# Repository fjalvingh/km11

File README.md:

# Pdp-11 KM11 Maintenance Module with LCD screen

This is supposed to become a KM11 maintenance module. It is a 2 slot card which should 
be placed in both KM11 slots of a PDP 11/05 or 11/10. It uses an ATTINY1616 (or 3216 
if I cannot make the code fit) and a set of i2c I/O adapters (PCF8574T) to read the data
from both slots for the KM11, and writes those to an LCD screen, offset on a cable.

The main PCB must be placed in the PDP 11/05. The LCD display and the switches sit on
a second, small PCB (`kicad/kmdisp`) at the end of a 20-way ribbon cable, so they can be
outside the pdp/11 in the 3D-printed console from `3d/`.

## Hardware

The board uses:

* An ATTINY1616 (or ATTINY3216) as the controller
* Six PCF8574T I2C extenders to connect to both KM11 slots
* A 1.8" 160x128 LCD display to show the data

## Schematic and PCB views, version 1.1

The first version had some small issues which were repaired in this version.

## Display and switches board

## Code

The code was partially created by Claude, and does not use the usual libraries to save space 
in the Flash memory of the ATTINY1616 as it only has 16K. The code directly accesses registers
to control both the ST7735 LCD controller and the I2C extenders, and contains three fonts (5x7,
8x14 and 8x16).

At the time of writing the code takes about 9.3KB of the 16KB Flash available.

The code is a loop that reads all six extenders about ten times a second and repaints only
what changed. The screen looks as follows:

### What the screen shows

```
CUR 301 H-1
AMUX 000000
SPAD R7  PC  spwr
ALU SF M c A
EALU butir msyn
auxc butjj ssyn
cnst butun bbsy
E OK        dati=0
MPC 302 H-2
```

* **CUR** – the microstep whose signals are on the rest of the screen (octal), with DEC's name
  for it as used in the microprogram flow charts. No lamp shows this: the firmware learns it
  from the MPC before a single step, so it reads `--` until it has seen one, and again while
  the clock runs.
* **AMUX** – the 16-bit data path (octal).
* **SPAD** – the scratchpad register being addressed, numbered as DEC does (R0–R17), with its
  use: SP, PC, SRC (R10), DST (R11), VEC (R12) or LAD (R17). Then SPWR, the scratchpad write.
* **ALU** – S, the raw S3–S0 function select (hex), then M (mode) and C (carry in), then the 74181 function they select (for example `A+B+1`). The function is grey when EALU is off, because then the ALU result does not reach the AMUX.
* **Flags**, in three columns: ALU/data path (EALU, AUXC, CNST), the microprogram branch tests
  (BUTIR, BUTJJ, BUTUN), and the Unibus (MSYN, SSYN, BBSY). Below the Unibus column is the bus
  cycle from C1/C0 with its code: DATI=0, DATIP=1, DATO=2, DATOB=3. The cycle name is lit while
  MSYN is asserted.
* **MPC** – the microprogram counter (octal), with its name. This is the *next* microstep, not
  the one whose signals are on the rest of the screen (KD11-B manual EK-KD11B-MM-001, 5.9).
* **Status** (below the first flag column) – the microcode revision and the result of the microcode check (see
  below). A red `I2C:` followed by U numbers replaces it when an extender does not answer; the
  values that extender supplies are then not real.

Signals that are active low on the backplane (and shown dim on the original KM11, like the MPC
and ALU S) are inverted first, so everything on the screen is the logical value. Single signals
are **yellow and upper case** when asserted, **red and lower case** when negated.

Colours that mark a value:

* **dark blue background** – changed since the machine last moved. When single stepping, this
  shows what the last step did, and it stays until the next step.
* **white on red** – does not match the microcode listing (see below).

### Microcode check

While the processor is single stepped (M CLK ENABLE on, M CLK PULSE to step), the firmware
compares the lamps with DEC's microcode listing for the microword that just executed. It checks
ALU S/M/C, the scratchpad address, the four BUT lamps and AUXC. The status shows:

| Status | Meaning |
| --- | --- |
| `E OK` / `F OK` | the lamps match the listing |
| `E BAD` | some lamps do not match; they are drawn white on red |
| `SEQ?` | the MPC moved to an address the previous microword cannot branch to; the MPC turns red |
| `--` | nothing to check: no step seen yet, or the clock is running |

The first letter is the microcode revision of the M7261: `E` (1973) or `F` (1976), or `?` until
it is known. The card finds out by itself. The two revisions differ only in 14 microwords, and
the first time a step passes one of them, the AUXC lamp shows which revision is installed. Unary
instructions (CLR, INC, COM…) pass them. The revision is kept in the ATtiny's EEPROM.
`make REV=E eeprom`, `make REV=F eeprom` or `make REV=AUTO eeprom` sets or forgets it. Uploading
new firmware erases it, and it is learnt again.

The four switches are BUS SSYN, AC LO, M CLK PULSE (STEP) and M CLK ENABLE. The AC LO one sits
on the KM11 pin the 11/20 used for NO TIMEOUT, and the net is still called `TIMEOUT_H` for that
reason; on the 11/05 throwing it asserts BUS AC LO and starts the power-fail sequence.

`review.md` records the September 2026 check of the design and firmware against DEC's own
documentation, with the sources.

## Help with microcode debugging

The PDP 11/05 microcode for Rev.E and Rev.F can be browsed easily using [the microcode browser for the PDP 11/05](https://tools.etc.to/).

## Programming

To program the ATTINY1616 please follow the setup and instructions from [my 8bit bus display tool](https://github.com/fjalvingh/8bit-busdisplay). The source code is under src/. Two steps to do for a build:

* Use `make` to build the code, then
* Use `make upload` to upload the code to the board (with the programmer connected, obviously).

## The prototype

I made a small test setup to test driving the display:

The initial idea was to use a fancy 2.25 landscape mode LCD to show the info, but after almost 4 hours
of testing and messing around with the code I gave up, I assume the display I got was defective. I was not helped by the fact that the second display tested, now the 1.8" display, was ALSO found to be defective, wasting another few hours. In the end I proved that of the 5 1.8" displays I have 1 was defective, and I had to pick that one for the test, obviously. Murphy in full working order.

## The first version in an actual PDP 11/10 (same as 11/05)

More closeup:

The microcode PC is at 302~oct~, which is H-2, part of the HALT instruction.

## Errata

The KM11 schematic in the 1973 manual shows V1 for M CLK L, the single step clock pulse. But this should be U1. The reproduction by [Tony Duell](http://www.ubanproductions.com/km11x.html) properly names U1 in the ascii art schematic for S4, but misnames it as J1 in the text.

In addition the S4 remark in the same thing seems to be wrong: the clock switch should be connected the other way around (i.e. latched upward in that schematic).

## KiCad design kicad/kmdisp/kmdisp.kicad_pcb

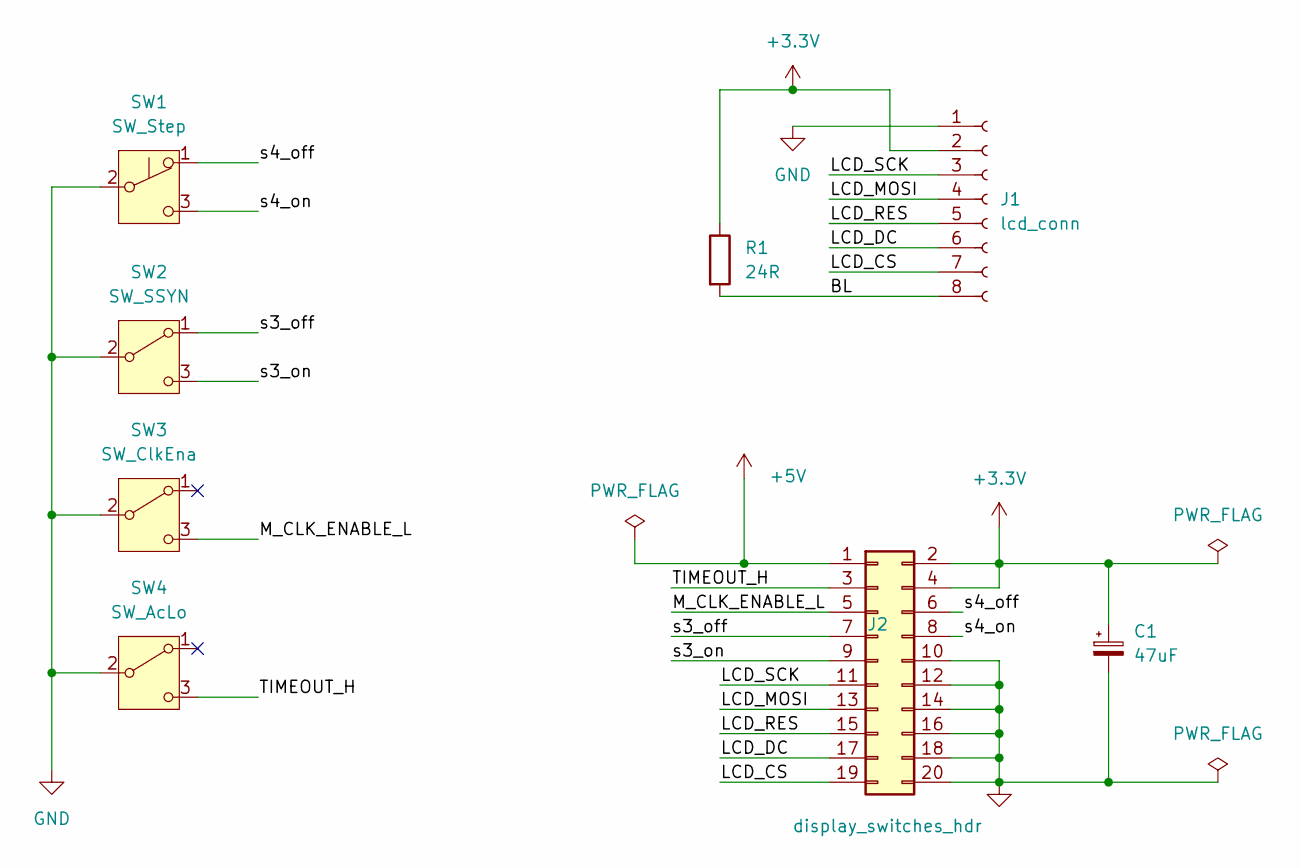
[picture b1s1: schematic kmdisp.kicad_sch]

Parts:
C1: 47uF; CP_Elec_4x3.9
J1: lcd_conn; PinSocket_1x08_P2.54mm_Vertical
J2: display_switches_hdr; PinHeader_2x10_P2.54mm_Vertical
R1: 24R; R_Axial_DIN0207_L6.3mm_D2.5mm_P7.62mm_Horizontal
SW1: SW_Step; SW_Toggle_MTS102
SW2: SW_SSYN; SW_Toggle_MTS102
SW3: SW_ClkEna; SW_Toggle_MTS102
SW4: SW_AcLo; SW_Toggle_MTS102

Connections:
+3.3V: C1.1, J1.2, J2.2, J2.4, R1.1
+5V: J2.1
/BL: J1.8, R1.2
/LCD_CS: J1.7, J2.19
/LCD_DC: J1.6, J2.17
/LCD_MOSI: J1.4, J2.13
/LCD_RES: J1.5, J2.15
/LCD_SCK: J1.3, J2.11
/M_CLK_ENABLE_L: J2.5, SW3.3 (C)
/TIMEOUT_H: J2.3, SW4.3 (C)
/s3_off: J2.7, SW2.1 (A)
/s3_on: J2.9, SW2.3 (C)
/s4_off: J2.6, SW1.1 (A)
/s4_on: J2.8, SW1.3 (C)
GND: C1.2, J1.1, J2.10, J2.12, J2.14, J2.16, J2.18, J2.20, SW1.2 (B), SW2.2 (B), SW3.2 (B), SW4.2 (B)

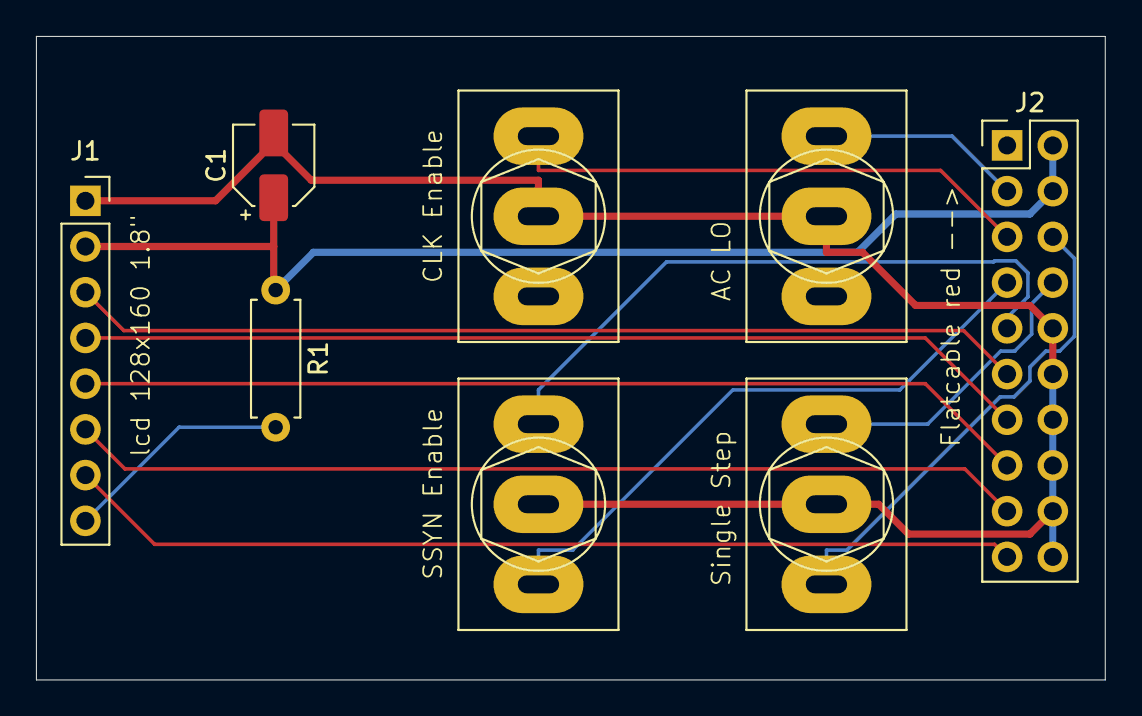
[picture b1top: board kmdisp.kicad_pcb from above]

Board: 2 copper layers, 59.4 x 35.8 mm, 8 parts (0 on the bottom side), 14 nets.

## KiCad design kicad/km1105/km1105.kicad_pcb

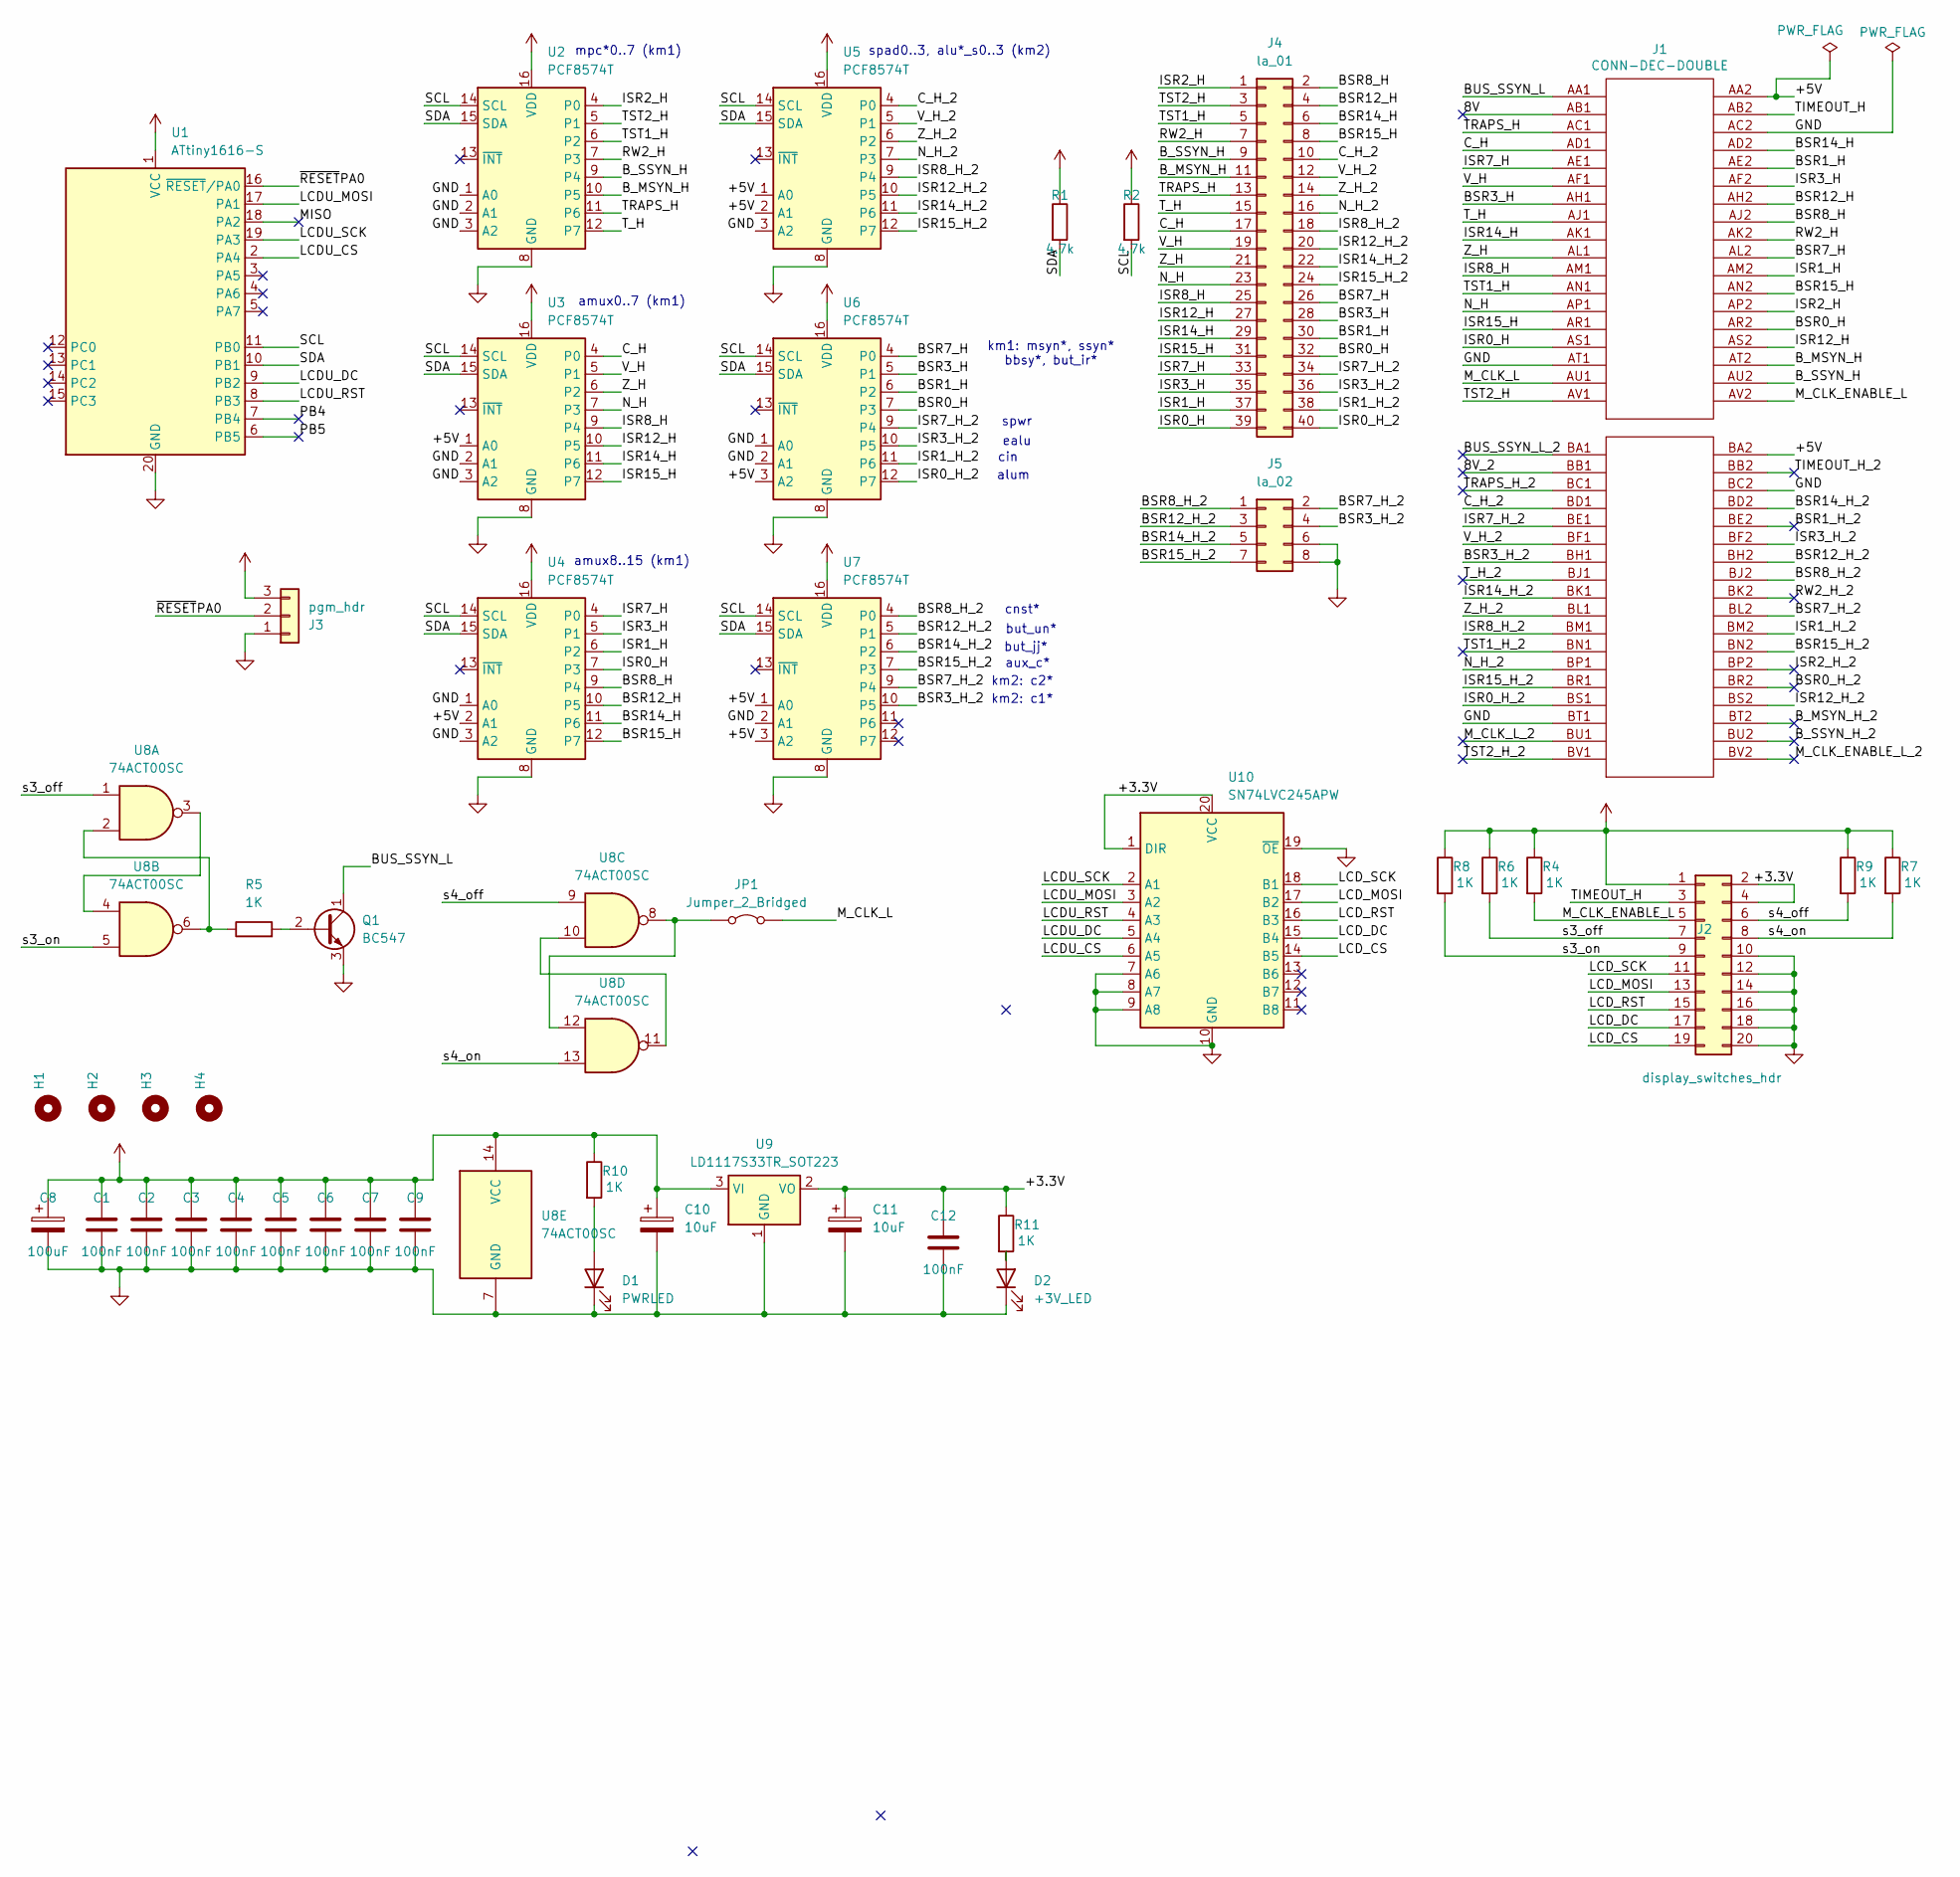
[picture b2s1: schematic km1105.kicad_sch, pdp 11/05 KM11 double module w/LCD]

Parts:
C1, C2, C3, C4, C5, C6, C7, C9, C12: 100nF; C_0805_2012Metric
C8: 100uF; CP_Elec_6.3x7.7
C10, C11: 10uF; CP_Elec_4x4.5
D1: PWRLED; LED_1206_3216Metric_Pad1.42x1.75mm_HandSolder
D2: +3V_LED; LED_1206_3216Metric_Pad1.42x1.75mm_HandSolder
H1, H2, H3, H4: MountingHole_3.2mm_M3
J1: CONN-DEC-DOUBLE
J2: display_switches_hdr; PinHeader_2x10_P2.54mm_Vertical
J3: pgm_hdr; PinHeader_1x03_P2.54mm_Vertical
J4: la_01; PinHeader_2x20_P2.54mm_Vertical
J5: la_02; PinHeader_2x04_P2.54mm_Vertical
JP1: Jumper_2_Bridged; SolderJumper-2_P1.3mm_Bridged_RoundedPad1.0x1.5mm
Q1: BC547; TO-92_Inline
R1, R2: 4.7k; R_0805_2012Metric
R4, R5, R6, R7, R8, R9, R10, R11: 1K; R_0805_2012Metric
U1: ATtiny1616-S; SOIC-20W_7.5x12.8mm_P1.27mm
U2, U3, U4, U5, U6, U7: PCF8574T; SOIC-16W_7.5x10.3mm_P1.27mm
U8: 74ACT00SC; SO-14_3.9x8.65mm_P1.27mm
U9: LD1117S33TR_SOT223; SOT-223-3_TabPin2
U10: SN74LVC245APW; TSSOP-20_4.4x6.5mm_P0.65mm

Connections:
+5V: C1.1, C2.1, C3.1, C4.1, C5.1, C6.1, C7.1, C8.1, C9.1, C10.1, J1.AA2, J1.BA2, J2.1, J3.3, R1.1, R2.1, R4.1, R6.1, R7.1, R8.1, R9.1, R10.1, U1.1 (VCC), U2.16 (VDD), U3.1 (A0), U3.16 (VDD), U4.2 (A1), U4.16 (VDD), U5.1 (A0), U5.2 (A1), U5.16 (VDD), U6.3 (A2), U6.16 (VDD), U7.1 (A0), U7.3 (A2), U7.16 (VDD), U8.14 (VCC), U9.3 (VI)
/8V: J1.AB1
/8V_2: J1.BB1
/+3.3V: C11.1, C12.1, J2.2, J2.4, R11.1, U9.2 (VO), U10.1 (DIR), U10.20 (VCC)
/BSR0_H: J1.AR2, J4.32, U6.7 (P3)
/BSR0_H_2: J1.BR2
/BSR1_H: J1.AE2, J4.30, U6.6 (P2)
/BSR1_H_2: J1.BE2
/BSR3_H: J1.AH1, J4.28, U6.5 (P1)
/BSR3_H_2: J1.BH1, J5.4, U7.10 (P5)
/BSR7_H: J1.AL2, J4.26, U6.4 (P0)
/BSR7_H_2: J1.BL2, J5.2, U7.9 (P4)
/BSR8_H: J1.AJ2, J4.2, U4.9 (P4)
/BSR8_H_2: J1.BJ2, J5.1, U7.4 (P0)
/BSR12_H: J1.AH2, J4.4, U4.10 (P5)
/BSR12_H_2: J1.BH2, J5.3, U7.5 (P1)
/BSR14_H: J1.AD2, J4.6, U4.11 (P6)
/BSR14_H_2: J1.BD2, J5.5, U7.6 (P2)
/BSR15_H: J1.AN2, J4.8, U4.12 (P7)
/BSR15_H_2: J1.BN2, J5.7, U7.7 (P3)
/BUS_SSYN_L: J1.AA1, Q1.1 (C)
/BUS_SSYN_L_2: J1.BA1
/B_MSYN_H: J1.AT2, J4.11, U2.10 (P5)
/B_MSYN_H_2: J1.BT2
/B_SSYN_H: J1.AU2, J4.9, U2.9 (P4)
/B_SSYN_H_2: J1.BU2
/C_H: J1.AD1, J4.17, U3.4 (P0)
/C_H_2: J1.BD1, J4.10, U5.4 (P0)
/ISR0_H: J1.AS1, J4.39, U4.7 (P3)
/ISR0_H_2: J1.BS1, J4.40, U6.12 (P7)
/ISR1_H: J1.AM2, J4.37, U4.6 (P2)
/ISR1_H_2: J1.BM2, J4.38, U6.11 (P6)
/ISR2_H: J1.AP2, J4.1, U2.4 (P0)
/ISR2_H_2: J1.BP2
/ISR3_H: J1.AF2, J4.35, U4.5 (P1)
/ISR3_H_2: J1.BF2, J4.36, U6.10 (P5)
/ISR7_H: J1.AE1, J4.33, U4.4 (P0)
/ISR7_H_2: J1.BE1, J4.34, U6.9 (P4)
/ISR8_H: J1.AM1, J4.25, U3.9 (P4)
/ISR8_H_2: J1.BM1, J4.18, U5.9 (P4)
/ISR12_H: J1.AS2, J4.27, U3.10 (P5)
/ISR12_H_2: J1.BS2, J4.20, U5.10 (P5)
/ISR14_H: J1.AK1, J4.29, U3.11 (P6)
/ISR14_H_2: J1.BK1, J4.22, U5.11 (P6)
/ISR15_H: J1.AR1, J4.31, U3.12 (P7)
/ISR15_H_2: J1.BR1, J4.24, U5.12 (P7)
/LCDU_CS: U1.2 (PA4), U10.6 (A5)
/LCDU_DC: U1.9 (PB2), U10.5 (A4)
/LCDU_MOSI: U1.17 (PA1), U10.3 (A2)
/LCDU_RST: U1.8 (PB3), U10.4 (A3)
/LCDU_SCK: U1.19 (PA3), U10.2 (A1)
/LCD_CS: J2.19, U10.14 (B5)
/LCD_DC: J2.17, U10.15 (B4)
/LCD_MOSI: J2.13, U10.17 (B2)
/LCD_RST: J2.15, U10.16 (B3)
/LCD_SCK: J2.11, U10.18 (B1)
/MISO: U1.18 (PA2)
/M_CLK_ENABLE_L: J1.AV2, J2.5, R4.2
/M_CLK_ENABLE_L_2: J1.BV2
/M_CLK_L: J1.AU1, JP1.2 (B)
/M_CLK_L_2: J1.BU1
/N_H: J1.AP1, J4.23, U3.7 (P3)
/N_H_2: J1.BP1, J4.16, U5.7 (P3)
/PB4: U1.7 (PB4)
/PB5: U1.6 (PB5)
/RW2_H: J1.AK2, J4.7, U2.7 (P3)
/RW2_H_2: J1.BK2
/SCL: R2.2, U1.11 (PB0), U2.14 (SCL), U3.14 (SCL), U4.14 (SCL), U5.14 (SCL), U6.14 (SCL), U7.14 (SCL)
/SDA: R1.2, U1.10 (PB1), U2.15 (SDA), U3.15 (SDA), U4.15 (SDA), U5.15 (SDA), U6.15 (SDA), U7.15 (SDA)
/TIMEOUT_H: J1.AB2, J2.3
/TIMEOUT_H_2: J1.BB2
/TRAPS_H: J1.AC1, J4.13, U2.11 (P6)
/TRAPS_H_2: J1.BC1
/TST1_H: J1.AN1, J4.5, U2.6 (P2)
/TST1_H_2: J1.BN1
/TST2_H: J1.AV1, J4.3, U2.5 (P1)
/TST2_H_2: J1.BV1
/T_H: J1.AJ1, J4.15, U2.12 (P7)
/T_H_2: J1.BJ1
/V_H: J1.AF1, J4.19, U3.5 (P1)
/V_H_2: J1.BF1, J4.12, U5.5 (P1)
/Z_H: J1.AL1, J4.21, U3.6 (P2)
/Z_H_2: J1.BL1, J4.14, U5.6 (P2)
/s3_off: J2.7, R6.2, U8.1
/s3_on: J2.9, R8.2, U8.5
/s4_off: J2.6, R9.2, U8.9
/s4_on: J2.8, R7.2, U8.13
/~RESETPA0: J3.2, U1.16 (~RESET/PA0)
GND: C1.2, C2.2, C3.2, C4.2, C5.2, C6.2, C7.2, C8.2, C9.2, C10.2, C11.2, C12.2, D1.1 (K), D2.1 (K), J1.AC2, J1.AT1, J1.BC2, J1.BT1, J2.10, J2.12, J2.14, J2.16, J2.18, J2.20, J3.1, J5.6, J5.8, Q1.3 (E), U1.20 (GND), U2.1 (A0), U2.2 (A1), U2.3 (A2), U2.8 (GND), U3.2 (A1), U3.3 (A2), U3.8 (GND), U4.1 (A0), U4.3 (A2), U4.8 (GND), U5.3 (A2), U5.8 (GND), U6.1 (A0), U6.2 (A1), U6.8 (GND), U7.2 (A1), U7.8 (GND), U8.7 (GND), U9.1 (GND), U10.7 (A6), U10.8 (A7), U10.9 (A8), U10.10 (GND), U10.19 (~OE)
unnamed: D1.2 (A), R10.2
unnamed: D2.2 (A), R11.2
unnamed: JP1.1 (A), U8.8, U8.12
unnamed: Q1.2 (B), R5.2
unnamed: R5.1, U8.2, U8.6
unnamed: U8.3, U8.4
unnamed: U8.10, U8.11

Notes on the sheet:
cin
but_un*
km2: c1*
but_jj*
amux8..15 (km1)
spwr
ealu
alum
amux0..7 (km1)
km2: c2*
spad0..3, alu*_s0..3 (km2)
km1: msyn*, ssyn* bbsy*, but_ir*
aux_c*
mpc*0..7 (km1)
cnst*

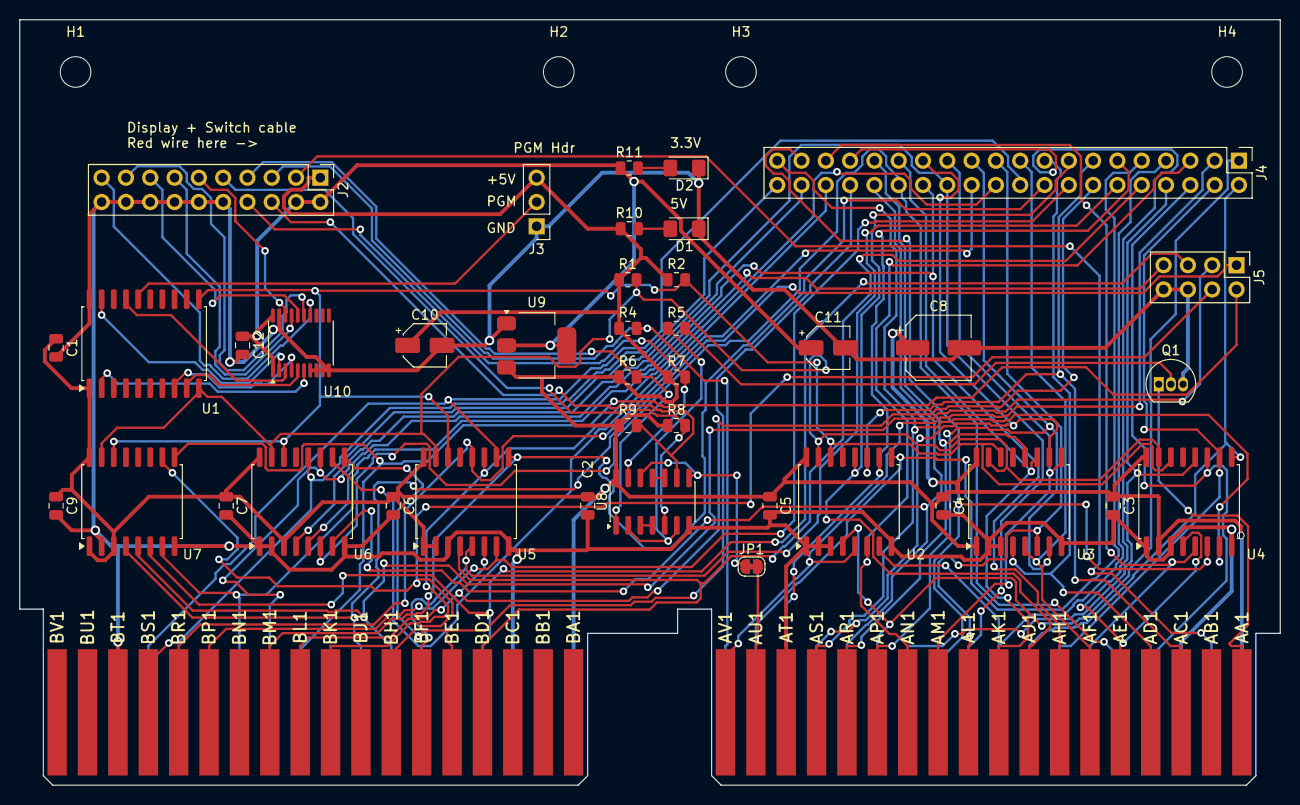
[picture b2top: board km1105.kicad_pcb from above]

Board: 2 copper layers, 131.7 x 80.0 mm, 45 parts (0 on the bottom side), 77 nets.

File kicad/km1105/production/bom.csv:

Designator,Footprint,Quantity,Value,LCSC Part #
"C1, C12, C2, C3, C4, C5, C6, C7, C9",0805,9,100nF,
"C10, C11",CP_Elec_4x4.5,2,10uF,
C8,CP_Elec_6.3x7.7,1,100uF,
D1,1206,1,PWRLED,
D2,1206,1,+3V_LED,
J1,CONN-DEC-DOUBLE,1,CONN-DEC-DOUBLE,
J2,PinHeader_2x10_P2.54mm_Vertical,1,display_switches_hdr,
J3,PinHeader_1x03_P2.54mm_Vertical,1,pgm_hdr,
J4,PinHeader_2x20_P2.54mm_Vertical,1,la_01,
J5,PinHeader_2x04_P2.54mm_Vertical,1,la_02,
JP1,SolderJumper-2_P1.3mm_Bridged_RoundedPad1.0x1.5mm,1,Jumper_2_Bridged,
Q1,TO-92_Inline,1,BC547,
"R1, R2",0805,2,4.7k,
"R10, R11, R4, R5, R6, R7, R8, R9",0805,8,1K,
U1,SOIC-20W_7.5x12.8mm_P1.27mm,1,ATtiny1616-S,
U10,TSSOP-20_4.4x6.5mm_P0.65mm,1,SN74LVC245APW,
"U2, U3, U4, U5, U6, U7",SOIC-16W_7.5x10.3mm_P1.27mm,6,PCF8574T,
U8,SO-14_3.9x8.65mm_P1.27mm,1,74ACT00SC,
U9,SOT-223-3_TabPin2,1,LD1117S33TR_SOT223,

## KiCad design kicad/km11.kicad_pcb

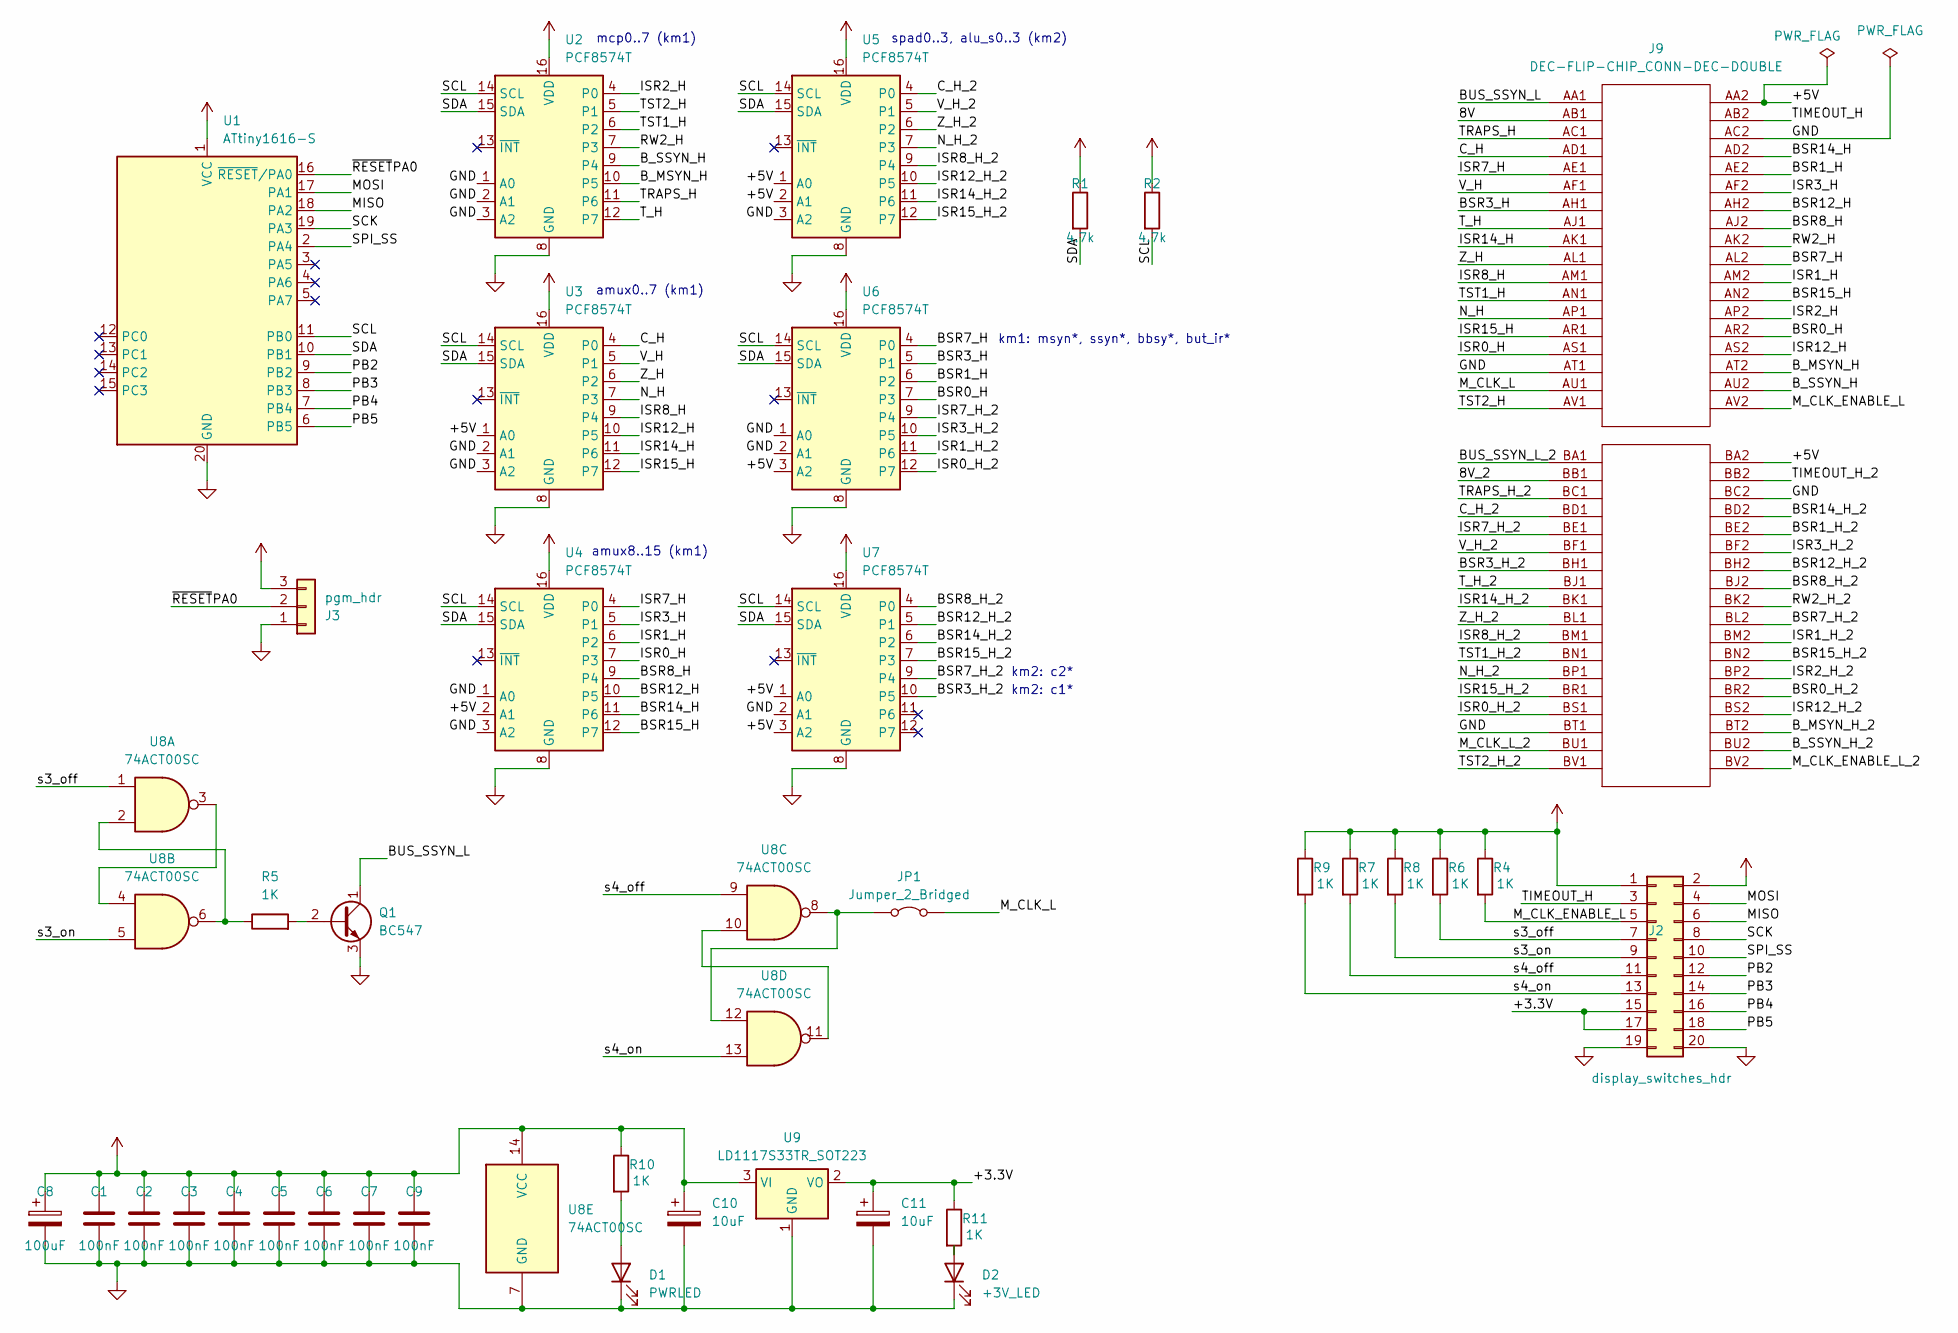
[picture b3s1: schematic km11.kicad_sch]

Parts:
C1, C2, C3, C4, C5, C6, C7, C9: 100nF; C_0805_2012Metric
C8: 100uF; CP_Elec_6.3x7.7
C10, C11: 10uF; CP_Elec_8x5.4
D1: PWRLED; LED_1206_3216Metric_Pad1.42x1.75mm_HandSolder
D2: +3V_LED; LED_1206_3216Metric_Pad1.42x1.75mm_HandSolder
J2: display_switches_hdr; PinHeader_2x10_P2.54mm_Vertical
J3: pgm_hdr; PinHeader_1x03_P2.54mm_Vertical
J9: DEC-FLIP-CHIP_CONN-DEC-DOUBLE; CONN-DEC-DOUBLE
JP1: Jumper_2_Bridged; SolderJumper-2_P1.3mm_Bridged_RoundedPad1.0x1.5mm
Q1: BC547; TO-92_Inline
R1, R2: 4.7k; R_0805_2012Metric
R4, R5, R6, R7, R8, R9, R10, R11: 1K; R_0805_2012Metric
U1: ATtiny1616-S; SOIC-20W_7.5x12.8mm_P1.27mm
U2, U3, U4, U5, U6, U7: PCF8574T; SOIC-16W_7.5x10.3mm_P1.27mm
U8: 74ACT00SC; SOIC-14W_7.5x9mm_P1.27mm
U9: LD1117S33TR_SOT223; SOT-223-3_TabPin2

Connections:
+5V: C1.1, C2.1, C3.1, C4.1, C5.1, C6.1, C7.1, C8.1, C9.1, C10.1, J2.1, J2.2, J3.3, J9.AA2, J9.BA2, R1.1, R2.1, R4.1, R6.1, R7.1, R8.1, R9.1, R10.1, U1.1 (VCC), U2.16 (VDD), U3.1 (A0), U3.16 (VDD), U4.2 (A1), U4.16 (VDD), U5.1 (A0), U5.2 (A1), U5.16 (VDD), U6.3 (A2), U6.16 (VDD), U7.1 (A0), U7.3 (A2), U7.16 (VDD), U8.14 (VCC), U9.3 (VI)
/8V: J9.AB1
/8V_2: J9.BB1
/+3.3V: C11.1, J2.15, J2.17, R11.1, U9.2 (VO)
/BSR0_H: J9.AR2, U6.7 (P3)
/BSR0_H_2: J9.BR2
/BSR1_H: J9.AE2, U6.6 (P2)
/BSR1_H_2: J9.BE2
/BSR3_H: J9.AH1, U6.5 (P1)
/BSR3_H_2: J9.BH1, U7.10 (P5)
/BSR7_H: J9.AL2, U6.4 (P0)
/BSR7_H_2: J9.BL2, U7.9 (P4)
/BSR8_H: J9.AJ2, U4.9 (P4)
/BSR8_H_2: J9.BJ2, U7.4 (P0)
/BSR12_H: J9.AH2, U4.10 (P5)
/BSR12_H_2: J9.BH2, U7.5 (P1)
/BSR14_H: J9.AD2, U4.11 (P6)
/BSR14_H_2: J9.BD2, U7.6 (P2)
/BSR15_H: J9.AN2, U4.12 (P7)
/BSR15_H_2: J9.BN2, U7.7 (P3)
/BUS_SSYN_L: J9.AA1, Q1.1 (C)
/BUS_SSYN_L_2: J9.BA1
/B_MSYN_H: J9.AT2, U2.10 (P5)
/B_MSYN_H_2: J9.BT2
/B_SSYN_H: J9.AU2, U2.9 (P4)
/B_SSYN_H_2: J9.BU2
/C_H: J9.AD1, U3.4 (P0)
/C_H_2: J9.BD1, U5.4 (P0)
/ISR0_H: J9.AS1, U4.7 (P3)
/ISR0_H_2: J9.BS1, U6.12 (P7)
/ISR1_H: J9.AM2, U4.6 (P2)
/ISR1_H_2: J9.BM2, U6.11 (P6)
/ISR2_H: J9.AP2, U2.4 (P0)
/ISR2_H_2: J9.BP2
/ISR3_H: J9.AF2, U4.5 (P1)
/ISR3_H_2: J9.BF2, U6.10 (P5)
/ISR7_H: J9.AE1, U4.4 (P0)
/ISR7_H_2: J9.BE1, U6.9 (P4)
/ISR8_H: J9.AM1, U3.9 (P4)
/ISR8_H_2: J9.BM1, U5.9 (P4)
/ISR12_H: J9.AS2, U3.10 (P5)
/ISR12_H_2: J9.BS2, U5.10 (P5)
/ISR14_H: J9.AK1, U3.11 (P6)
/ISR14_H_2: J9.BK1, U5.11 (P6)
/ISR15_H: J9.AR1, U3.12 (P7)
/ISR15_H_2: J9.BR1, U5.12 (P7)
/MISO: J2.6, U1.18 (PA2)
/MOSI: J2.4, U1.17 (PA1)
/M_CLK_ENABLE_L: J2.5, J9.AV2, R4.2
/M_CLK_ENABLE_L_2: J9.BV2
/M_CLK_L: J9.AU1, JP1.2 (B)
/M_CLK_L_2: J9.BU1
/N_H: J9.AP1, U3.7 (P3)
/N_H_2: J9.BP1, U5.7 (P3)
/PB2: J2.12, U1.9 (PB2)
/PB3: J2.14, U1.8 (PB3)
/PB4: J2.16, U1.7 (PB4)
/PB5: J2.18, U1.6 (PB5)
/RW2_H: J9.AK2, U2.7 (P3)
/RW2_H_2: J9.BK2
/SCK: J2.8, U1.19 (PA3)
/SCL: R2.2, U1.11 (PB0), U2.14 (SCL), U3.14 (SCL), U4.14 (SCL), U5.14 (SCL), U6.14 (SCL), U7.14 (SCL)
/SDA: R1.2, U1.10 (PB1), U2.15 (SDA), U3.15 (SDA), U4.15 (SDA), U5.15 (SDA), U6.15 (SDA), U7.15 (SDA)
/SPI_SS: J2.10, U1.2 (PA4)
/TIMEOUT_H: J2.3, J9.AB2
/TIMEOUT_H_2: J9.BB2
/TRAPS_H: J9.AC1, U2.11 (P6)
/TRAPS_H_2: J9.BC1
/TST1_H: J9.AN1, U2.6 (P2)
/TST1_H_2: J9.BN1
/TST2_H: J9.AV1, U2.5 (P1)
/TST2_H_2: J9.BV1
/T_H: J9.AJ1, U2.12 (P7)
/T_H_2: J9.BJ1
/V_H: J9.AF1, U3.5 (P1)
/V_H_2: J9.BF1, U5.5 (P1)
/Z_H: J9.AL1, U3.6 (P2)
/Z_H_2: J9.BL1, U5.6 (P2)
/s3_off: J2.7, R6.2, U8.1
/s3_on: J2.9, R8.2, U8.5
/s4_off: J2.11, R7.2, U8.9
/s4_on: J2.13, R9.2, U8.13
/~RESETPA0: J3.2, U1.16 (~RESET/PA0)
GND: C1.2, C2.2, C3.2, C4.2, C5.2, C6.2, C7.2, C8.2, C9.2, C10.2, C11.2, D1.1 (K), D2.1 (K), J2.19, J2.20, J3.1, J9.AC2, J9.AT1, J9.BC2, J9.BT1, Q1.3 (E), U1.20 (GND), U2.1 (A0), U2.2 (A1), U2.3 (A2), U2.8 (GND), U3.2 (A1), U3.3 (A2), U3.8 (GND), U4.1 (A0), U4.3 (A2), U4.8 (GND), U5.3 (A2), U5.8 (GND), U6.1 (A0), U6.2 (A1), U6.8 (GND), U7.2 (A1), U7.8 (GND), U8.7 (GND), U9.1 (GND)
unnamed: D1.2 (A), R10.2
unnamed: D2.2 (A), R11.2
unnamed: JP1.1 (A), U8.8, U8.12
unnamed: Q1.2 (B), R5.2
unnamed: R5.1, U8.2, U8.6
unnamed: U8.3, U8.4
unnamed: U8.10, U8.11

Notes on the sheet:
km2: c2*
mcp0..7 (km1)
amux8..15 (km1)
amux0..7 (km1)
spad0..3, alu_s0..3 (km2)
km1: msyn*, ssyn*, bbsy*, but_ir*
km2: c1*

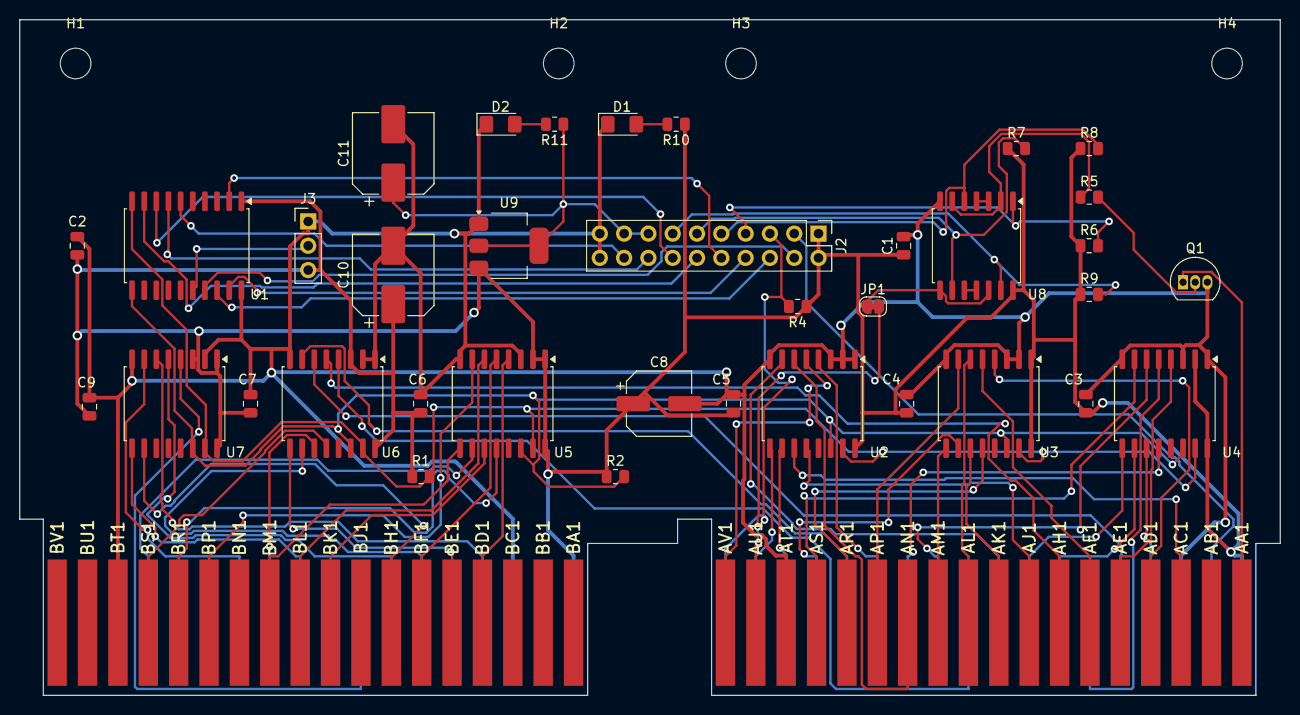
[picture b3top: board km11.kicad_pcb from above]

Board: 2 copper layers, 131.7 x 70.6 mm, 41 parts (0 on the bottom side), 75 nets.

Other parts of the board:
H1, H2, H3, H4: MountingHole_3.2mm_M3

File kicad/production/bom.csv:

Designator,Footprint,Quantity,Value,LCSC Part #
"C1, C2, C3, C4, C5, C6, C7, C9",0805,8,100nF,
"C10, C11",CP_Elec_8x5.4,2,10uF,
C8,CP_Elec_6.3x7.7,1,100uF,
D1,1206,1,PWRLED,
D2,1206,1,+3V_LED,
J1,CONN-DEC-DOUBLE,1,CONN-DEC-DOUBLE,
J2,PinHeader_2x10_P2.54mm_Vertical,1,display_switches_hdr,
J3,PinHeader_1x03_P2.54mm_Vertical,1,pgm_hdr,
JP1,SolderJumper-2_P1.3mm_Bridged_RoundedPad1.0x1.5mm,1,Jumper_2_Bridged,
Q1,TO-92_Inline,1,BC547,
"R1, R2",0805,2,4.7k,
"R10, R11, R4, R5, R6, R7, R8, R9",0805,8,1K,
U1,SOIC-20W_7.5x12.8mm_P1.27mm,1,ATtiny1616-S,
"U2, U3, U4, U5, U6, U7",SOIC-16W_7.5x10.3mm_P1.27mm,6,PCF8574T,
U8,SOIC-14W_7.5x9mm_P1.27mm,1,74ACT00SC,
U9,SOT-223-3_TabPin2,1,LD1117S33TR_SOT223,

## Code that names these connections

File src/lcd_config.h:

#ifndef LCD_CONFIG_H
#define LCD_CONFIG_H

// Hardware configuration for the KM11 display, taken from kicad/km1105 (the
// card) and kicad/kmdisp (the display board at the far end of the ribbon).
//
// The ATtiny1616 talks to the panel over SPI0 on its default port A mux, so no
// PORTMUX change is needed. Every display line leaves the ATtiny at 5V, goes
// through U10 (74LVC245 on the 3.3V rail) and reaches the ribbon header J2 at
// 3.3V; the display board's J2 has the same pinout and passes it straight to
// the module socket J1:
//
//   PA1  MOSI  -> U10 A2/B2 -> J2.13 -> kmdisp J1.4 (SDA)
//   PA2  MISO                            (unused by the display, it is write-only;
//                                         not on the ribbon)
//   PA3  SCK   -> U10 A1/B1 -> J2.11 -> kmdisp J1.3 (SCL)
//   PA4  SS    -> U10 A5/B5 -> J2.19 -> kmdisp J1.7 (CS), software controlled
//                                         (SPI0 SSD is set)
//   PB2  DC    -> U10 A4/B4 -> J2.17 -> kmdisp J1.6
//   PB3  RST   -> U10 A3/B3 -> J2.15 -> kmdisp J1.5, active low
//
// Every even J2 pin from 10 to 20 is GND, so each signal has a return next to
// it in the ribbon. The backlight is fed on the display board (J1.8 via R1 from
// +3.3V), so there is no pin for it here. PB4 and PB5 are spare and do not go
// to the ribbon; probe them at the chip.

#define LCD_SPI_PORT    PORTA
#define LCD_MOSI_bm     PIN1_bm
#define LCD_SCK_bm      PIN3_bm
#define LCD_CS_bm       PIN4_bm

#define LCD_CTRL_PORT   PORTB
#define LCD_DC_bm       PIN2_bm
#define LCD_RST_bm      PIN3_bm

// ---------------------------------------------------------------- the panel
//
// Two panels are described below; LCD_CONTROLLER picks one and everything else
// follows from it. The ST7735 is the 1.8" 128x160 board the KM11 uses - the
// display board and the 3d/ console are made for it. The ST7789P3 entry is a
// 2.25" 76x284 panel that was tried early on and never produced an image; it
// is kept for reference only.

#define LCD_ST7789      0
#define LCD_ST7735      1

#define LCD_CONTROLLER  LCD_ST7735

#if LCD_CONTROLLER == LCD_ST7789

// M35-2.25TFT-lanban, 2.25", 76x284 pixels, ST7789P3 controller.
#define LCD_PANEL_W     76
#define LCD_PANEL_H     284

// The ST7789 has 240x320 of frame memory and this panel is wired to a window
// inside it, so every address has to be shifted. These assume it sits centred:
// (240-76)/2 = 82 and (320-284)/2 = 18. Never confirmed on hardware - the panel
// has not produced an image yet.
#define LCD_COL_OFFSET  82
#define LCD_ROW_OFFSET  18

#define LCD_BGR         0
#define LCD_INVERT      1

// VCOM sets the LCD bias, and a value the glass does not like means no visible
// contrast at all - a controller that runs, accepts pixels and still shows
// plain white. Panel specific, and the first thing to sweep on a white screen:
// 0x19, 0x1A, 0x20, 0x28, 0x35.
#define LCD_VCOM        0x35

#else

// ST7735 board. Which panel it carries decides the size and the offsets, and
// the two common ones do not agree on either.
//
// 80x160 is the 0.96" size, and it sits in the middle of the frame memory.
// 128x160 is the classic 1.8" board, and it starts at the origin. A 1.8" board
// is far more often 128x160, so if this one shows a band down one side, or the
// image is shifted right by about a quarter of the screen, set this to 0.
#define LCD_ST7735_80x160  0

#if LCD_ST7735_80x160
	#define LCD_PANEL_W     80
	#define LCD_PANEL_H     160

	// The ST7735 has 132x162 of frame memory and this panel sits centred in it:
	// (132-80)/2 = 26, and one row down.
	#define LCD_COL_OFFSET  26
	#define LCD_ROW_OFFSET  1
#else
	#define LCD_PANEL_W     128
	#define LCD_PANEL_H     160

	// 128x160 fills the memory from the origin. Some boards ("green tab") want
	// 2 and 1 instead; a two pixel shift at one edge is the symptom.
	#define LCD_COL_OFFSET  0
	#define LCD_ROW_OFFSET  0
#endif

// This panel is wired red-green-blue. With BGR set it showed red and blue
// exchanged and green untouched - blue came out red, yellow came out cyan -
// which is the signature of that one bit. Other modules of the same type are
// genuinely BGR, so this is worth flipping if a replacement swaps its primaries.
//
// Inversion is off: with it on, this one showed every primary as its
// complement - red as cyan, green as magenta, blue as yellow. Plenty of 80x160
// modules do want it on, so it is worth flipping if a replacement panel comes
// out looking negative.
#define LCD_BGR         0
#define LCD_INVERT      0

#endif

// 0 and 2 are portrait, 1 and 3 are landscape. Landscape on the 128x160 ST7735
// gives 26 columns x 16 lines of 5x7 text; on the 80x160 ST7735 26 columns x 10
// lines, and on the ST7789P3 panel 47 columns x 9 lines.
#define LCD_ROTATION    1

// Send the full init sequence (porch/frame rate, gate, VCOM, power and gamma)
// instead of the bare minimum of sleep-out, pixel format and display-on. With
// the power and VCOM registers left at their reset values a controller will
// happily run and accept pixels while driving the glass to plain white.
//
// Only consulted for the ST7789: the ST7735 needs its full sequence, and the
// minimal one is not offered for it.
#define LCD_FULL_INIT   1

// SPI mode. ST7789 clocks data in on the rising edge, which is mode 0 for an
// idle-low clock; a few modules only work in mode 3. Try 3 if the panel
// ignores everything even though data and clock look right on a scope.
#define LCD_SPI_MODE    0

// SPI clock divider off F_CPU: 4, 16, 64 or 128. At the 10MHz this runs at,
// that is 2.5MHz, 625kHz, 156kHz or 78kHz.
//
// Turn this DOWN, not up, when pixels come out missing or scrambled: if the
// artefacts change with the clock they are a timing or signal integrity
// problem, and if they do not change at all the fault is somewhere else
// entirely. A full screen at 128 takes several seconds, which is fine for a
// test and useless for anything else.
//
// Overridable from the command line without editing this file, so a long
// ribbon cable can be tried at every speed: make LCD_SPI_DIV=128 upload
#ifndef LCD_SPI_DIV
#define LCD_SPI_DIV     16
#endif

// Debug aid. DC is normally low for exactly one byte time (6.4us at 1.25MHz),
// which is far too short to spot on a scope that is not triggered on it. Set
// this to 1 to hold DC low for an extra 200us around every command byte, which
// makes the command phase plainly visible. Harmless to the protocol: the panel
// only samples DC on the clock edges, and the clock is idle during the delay.
#define LCD_STRETCH_DC  0

// Change DC only while CS is high, so that a clock glitch coupled from the DC
// edge into SCK on the ribbon falls on deaf ears. Costs a few hundred ns per
// command. Try this when the first pixels after a command come out wrong.
// make EXTRA=-DLCD_DC_UNDER_CS=1
#ifndef LCD_DC_UNDER_CS
#define LCD_DC_UNDER_CS 0
#endif

// Diagnostic: bit-bang everything open-drain, never driving a high, so the 5V
// ATtiny cannot push current into the 3.3V panel's input clamps. Slow (about
// 50kHz) and for testing only; see lcd.cpp. Normally set from the command line:
// make EXTRA=-DLCD_OPEN_DRAIN=1
#ifndef LCD_OPEN_DRAIN
#define LCD_OPEN_DRAIN  0
#endif

#endif // LCD_CONFIG_H

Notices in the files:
kicad/km1105/km1105.kicad_pcb:
(C)2026 ErrorSoft (etc.to)
